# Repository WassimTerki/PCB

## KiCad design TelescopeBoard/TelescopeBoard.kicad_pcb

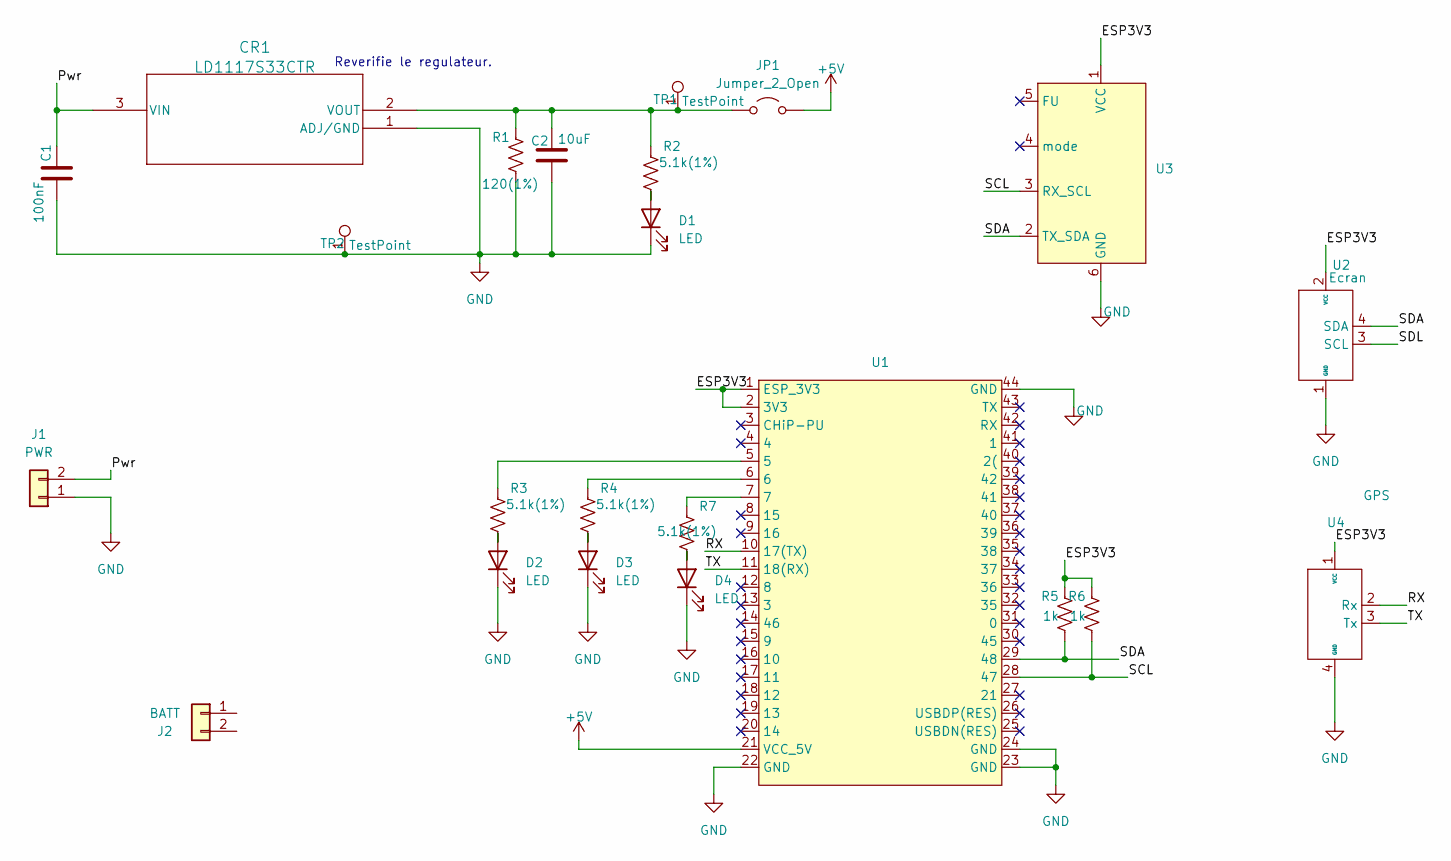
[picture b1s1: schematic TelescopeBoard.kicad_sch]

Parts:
C1: 100nF; C_0805_2012Metric_Pad1.18x1.45mm_HandSolder
C2: 10uF; C_0805_2012Metric_Pad1.18x1.45mm_HandSolder
CR1: LD1117S33CTR; careguleiciouuuuuuuuu
D1, D2, D3, D4: LED; LED_LTST-C_LTO
J1: PWR; PinHeader_1x02_P2.54mm_Vertical
J2: BATT; conn2
JP1: Jumper_2_Open; PinHeader_1x02_P2.54mm_Vertical
R1: 120(1%); R_0805_2012Metric
R2, R3, R4, R7: 5.1k(1%); R_0805_2012Metric
R5, R6: 1k; R_0805_2012Metric
TP1, TP2: TestPoint; PinHeader_1x01_P2.54mm_Vertical
U1: MY SHIT
U2: Ecran; PinHeader_1x04_P2.54mm_Vertical
U3: PinHeader_1x06_P2.54mm_Vertical
U4: GPS; PinHeader_1x04_P2.54mm_Vertical

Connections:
+5V: JP1.2 (B), U1.21 (VCC_5V)
/ESP3V3: R5.2, R6.2, U1.1 (ESP_3V3), U1.2 (3V3), U2.2 (VCC), U3.1 (VCC), U4.1 (VCC)
/Pwr: C1.1, CR1.3 (VIN), J1.2
/RX: U1.10 (17(TX)), U4.2 (Rx)
/SCL: R6.1, U1.28 (47), U3.3 (RX_SCL)
/SDA: R5.1, U1.29 (48), U2.4 (SDA), U3.2 (TX_SDA)
/SDL: U2.3 (SCL)
/TX: U1.11 (18(RX)), U4.3 (Tx)
GND: C1.2, C2.2, CR1.1 (ADJ/GND), D1.1 (K), D2.1 (K), D3.1 (K), D4.1 (K), J1.1, R1.1, TP2.1, U1.22 (GND), U1.23 (GND), U1.24 (GND), U1.44 (GND), U2.1 (GND), U3.6 (GND), U4.4 (GND)
unnamed: C2.1, CR1.2 (VOUT), JP1.1 (A), R1.2, R2.2, TP1.1
unnamed: D1.2 (A), R2.1
unnamed: D2.2 (A), R3.1
unnamed: D3.2 (A), R4.1
unnamed: D4.2 (A), R7.1
unnamed: R3.2, U1.5
unnamed: R4.2, U1.6
unnamed: R7.2, U1.7

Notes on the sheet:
Reverifie le regulateur.

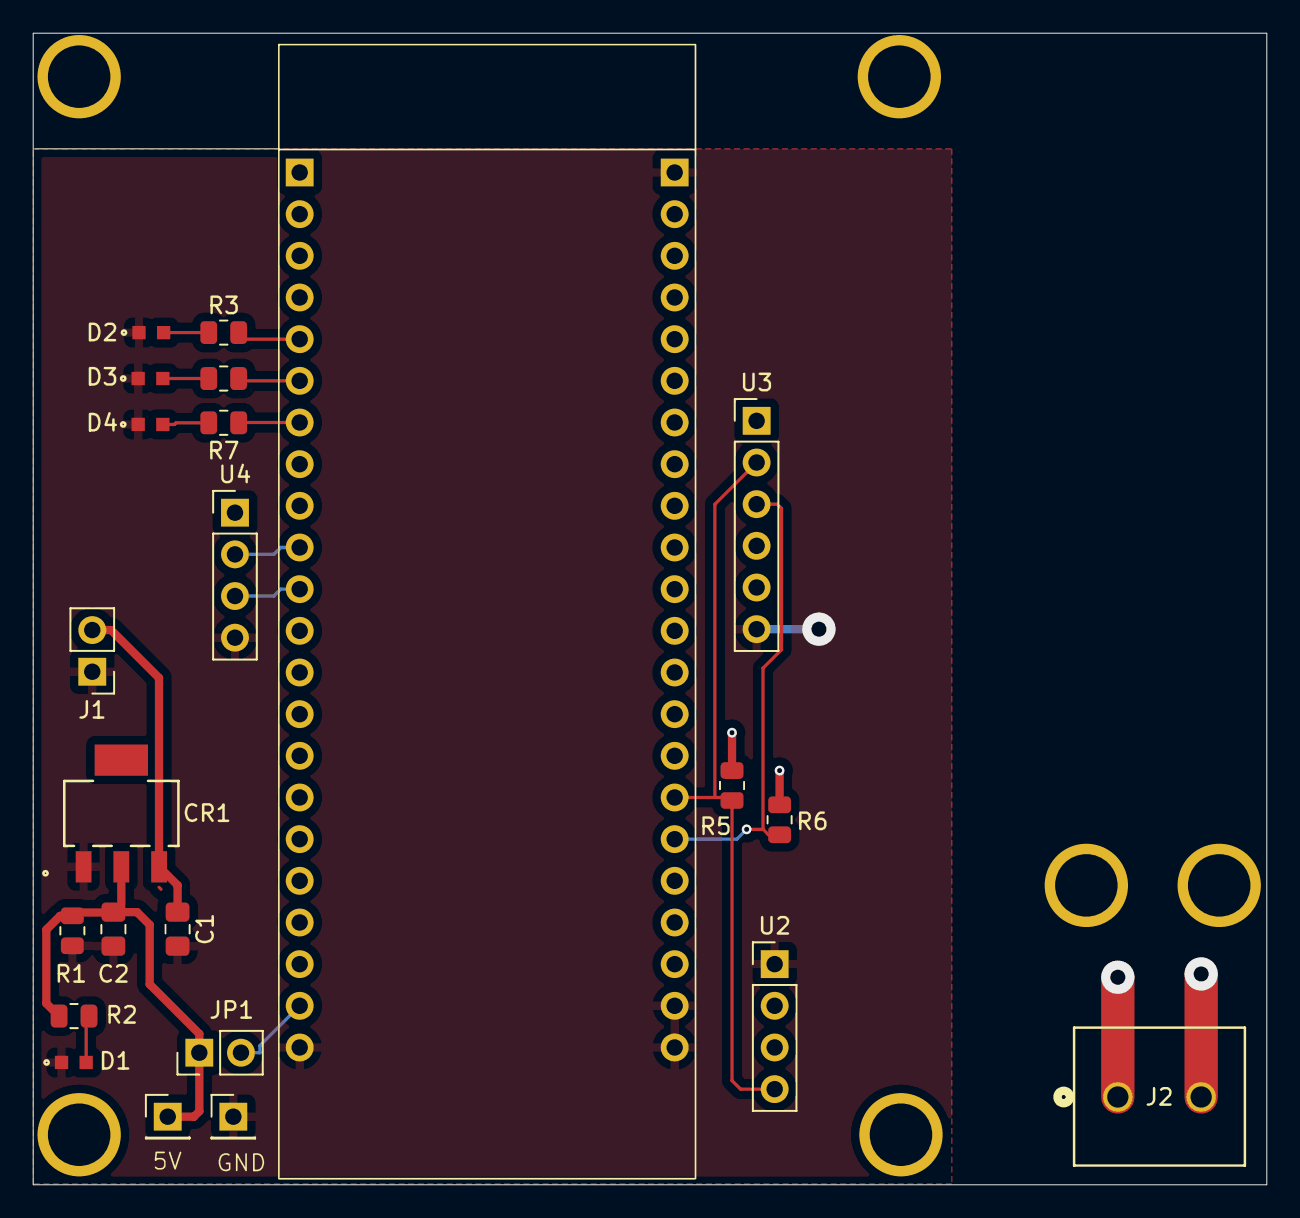
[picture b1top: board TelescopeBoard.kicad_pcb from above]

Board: 2 copper layers, 75.2 x 70.2 mm, 23 parts (0 on the bottom side), 16 nets.

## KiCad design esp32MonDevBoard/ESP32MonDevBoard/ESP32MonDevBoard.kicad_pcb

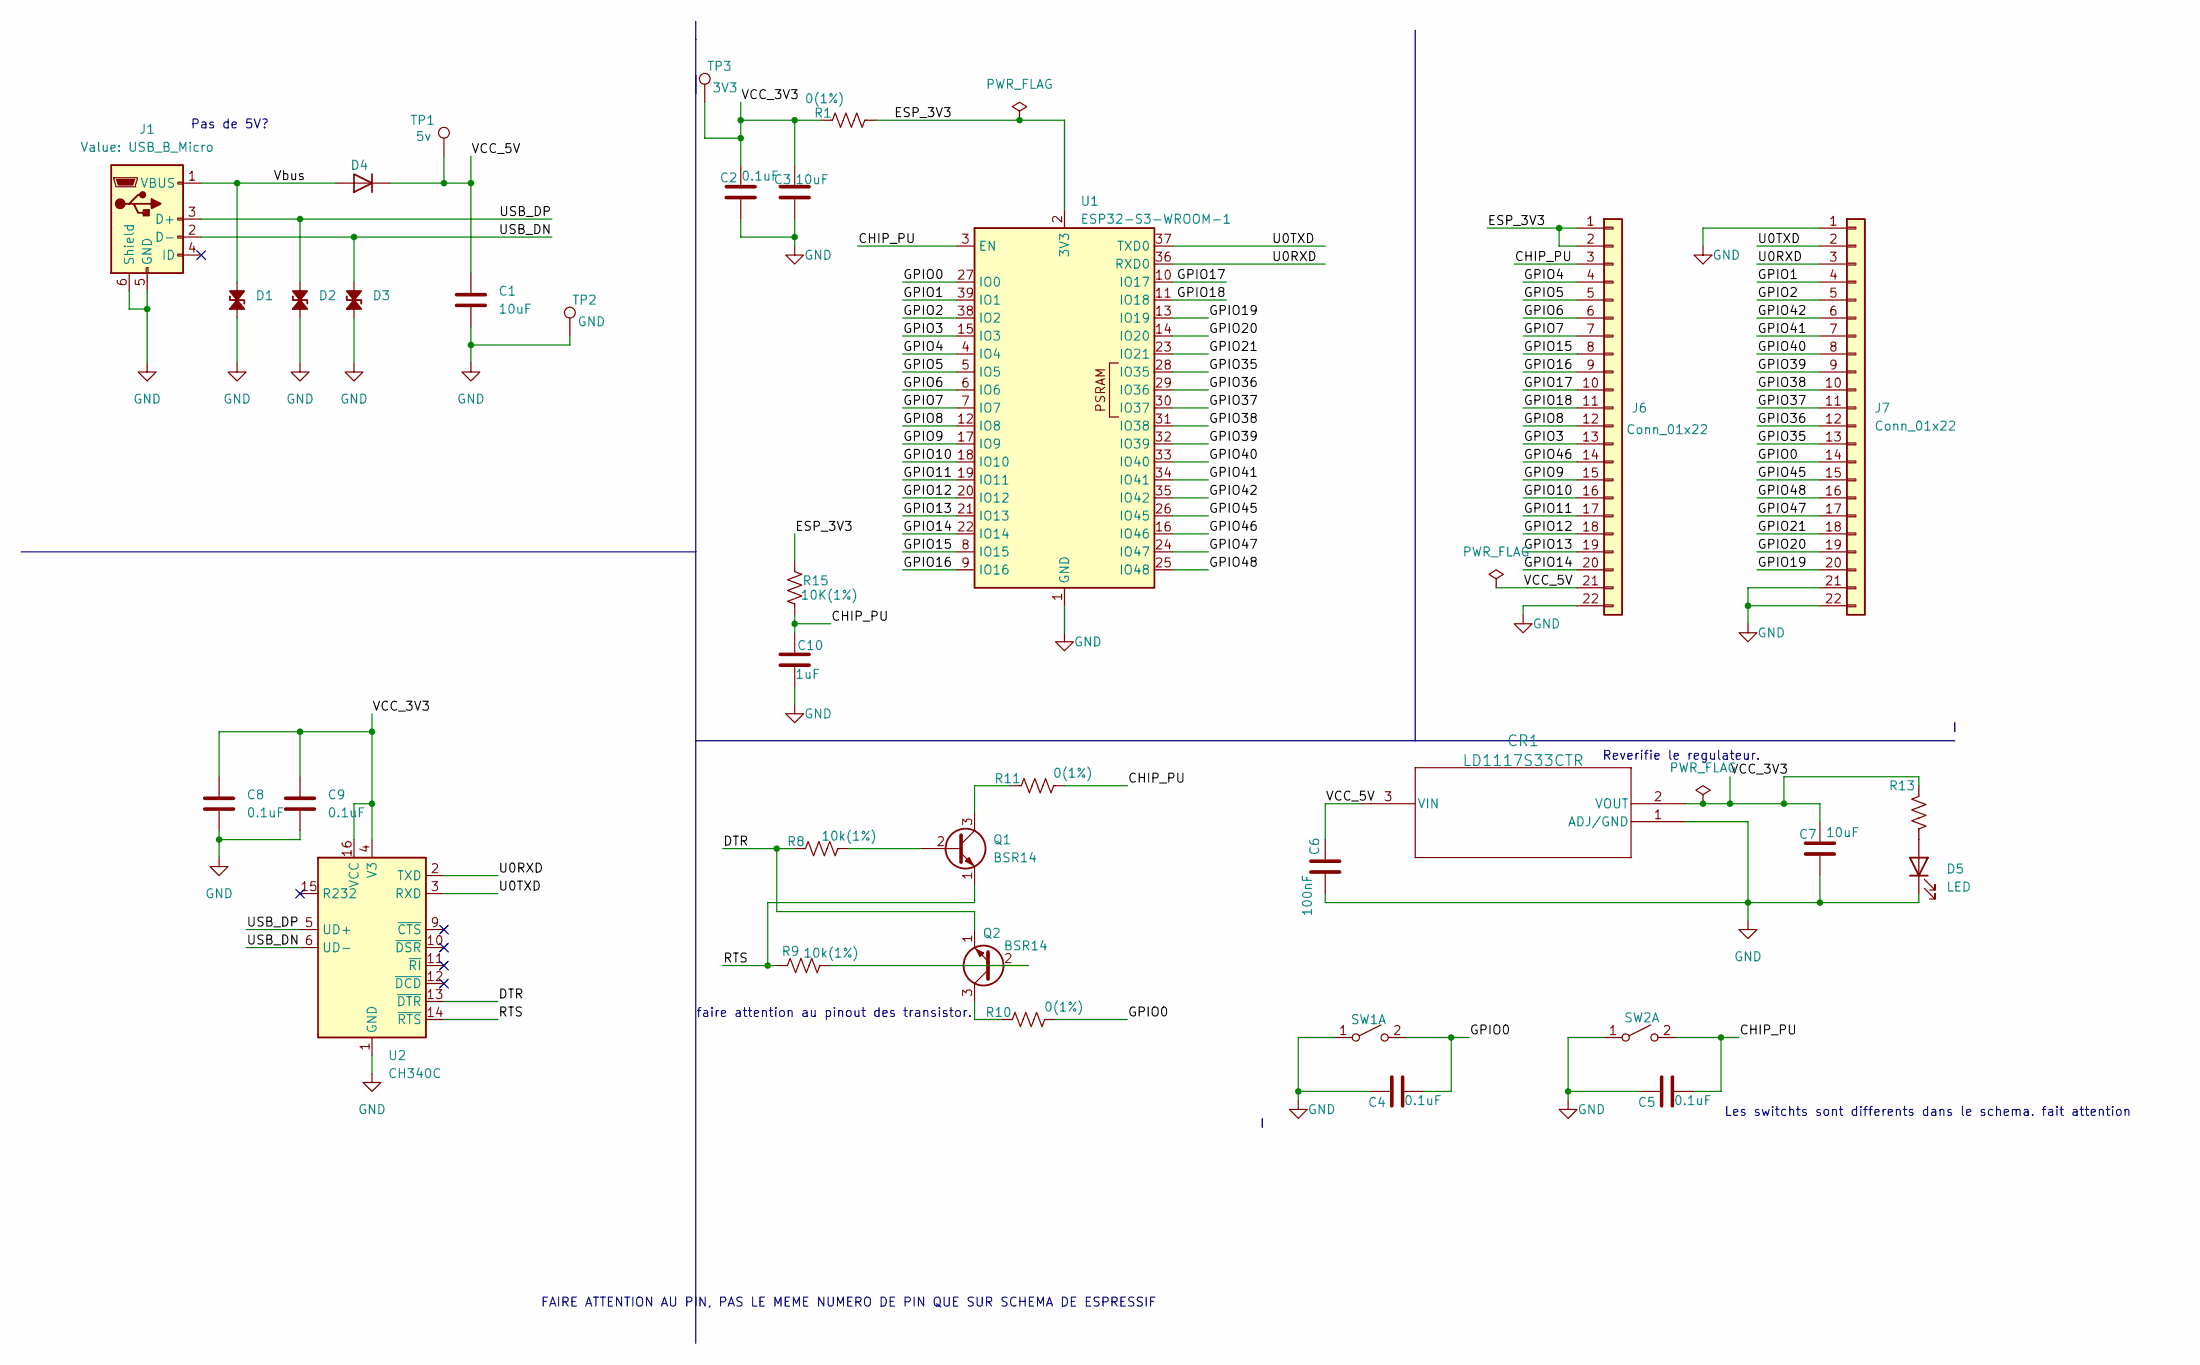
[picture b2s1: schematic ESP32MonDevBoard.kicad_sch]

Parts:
C1, C3, C7: 10uF; C_0805_2012Metric_Pad1.18x1.45mm_HandSolder
C2, C4, C5, C8, C9: 0.1uF; C_0805_2012Metric_Pad1.18x1.45mm_HandSolder
C6: 100nF; C_0805_2012Metric_Pad1.18x1.45mm_HandSolder
C10: 1uF; C_0805_2012Metric_Pad1.18x1.45mm_HandSolder
CR1: LD1117S33CTR; careguleiciouuuuuuuuu
D1, D2, D3: DODEBIZ
D4: dode
D5: LED; LED_LTST-C_LTO
J1: USB_B_Micro; CONN_10118192-0002LF_AMP
J6, J7: Conn_01x22; PinHeader_1x22_P2.54mm_Vertical
Q1, Q2: BSR14; transistor
R1, R10, R11: 0(1%); R_0805_2012Metric
R8, R9: 10k(1%); R_0805_2012Metric
R13: R_0805_2012Metric
R15: 10K(1%); R_0805_2012Metric
SW1, SW2: rien a signaler
TP1: 5v; PinHeader_1x01_P2.54mm_Vertical
TP2: GND; PinHeader_1x01_P2.54mm_Vertical
TP3: 3V3; PinHeader_1x01_P2.54mm_Vertical
U1: ESP32-S3-WROOM-1
U2: CH340C; SOIC-16_3.9x9.9mm_P1.27mm

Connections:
/CHIP_PU: C5.2, C10.1, J6.3, R11.2, R15.2, SW2.2 (B), U1.3 (EN)
/DTR: Q2.1 (E), R8.1, U2.13 (~DTR)
/ESP_3V3: J6.1, J6.2, R1.2, R15.1, U1.2 (3V3)
/GPIO0: C4.2, J7.14, R10.2, SW1.2 (B), U1.27 (IO0)
/GPIO1: J7.4, U1.39 (IO1)
/GPIO2: J7.5, U1.38 (IO2)
/GPIO3: J6.13, U1.15 (IO3)
/GPIO4: J6.4, U1.4 (IO4)
/GPIO5: J6.5, U1.5 (IO5)
/GPIO6: J6.6, U1.6 (IO6)
/GPIO7: J6.7, U1.7 (IO7)
/GPIO8: J6.12, U1.12 (IO8)
/GPIO9: J6.15, U1.17 (IO9)
/GPIO10: J6.16, U1.18 (IO10)
/GPIO11: J6.17, U1.19 (IO11)
/GPIO12: J6.18, U1.20 (IO12)
/GPIO13: J6.19, U1.21 (IO13)
/GPIO14: J6.20, U1.22 (IO14)
/GPIO15: J6.8, U1.8 (IO15)
/GPIO16: J6.9, U1.9 (IO16)
/GPIO17: J6.10, U1.10 (IO17)
/GPIO18: J6.11, U1.11 (IO18)
/GPIO19: J7.20, U1.13 (IO19)
/GPIO20: J7.19, U1.14 (IO20)
/GPIO21: J7.18, U1.23 (IO21)
/GPIO35: J7.13, U1.28 (IO35)
/GPIO36: J7.12, U1.29 (IO36)
/GPIO37: J7.11, U1.30 (IO37)
/GPIO38: J7.10, U1.31 (IO38)
/GPIO39: J7.9, U1.32 (IO39)
/GPIO40: J7.8, U1.33 (IO40)
/GPIO41: J7.7, U1.34 (IO41)
/GPIO42: J7.6, U1.35 (IO42)
/GPIO45: J7.15, U1.26 (IO45)
/GPIO46: J6.14, U1.16 (IO46)
/GPIO47: J7.17, U1.24 (IO47)
/GPIO48: J7.16, U1.25 (IO48)
/RTS: Q1.1 (E), R9.1, U2.14 (~RTS)
/U0RXD: J7.3, U1.36 (RXD0), U2.2 (TXD)
/U0TXD: J7.2, U1.37 (TXD0), U2.3 (RXD)
/USB_DN: D3.2 (A2), J1.2 (D-), U2.6 (UD-)
/USB_DP: D2.2 (A2), J1.3 (D+), U2.5 (UD+)
/VCC_3V3: C2.1, C3.1, C7.1, C8.1, C9.1, CR1.2 (VOUT), R1.1, R13.2, TP3.1, U2.4 (V3), U2.16 (VCC)
/VCC_5V: C1.1, C6.1, CR1.3 (VIN), D4.1 (K), J6.21, TP1.1
/Vbus: D1.2 (A2), D4.2 (A), J1.1 (VBUS)
GND: C1.2, C2.2, C3.2, C4.1, C5.1, C6.2, C7.2, C8.2, C9.2, C10.2, CR1.1 (ADJ/GND), D1.1 (A1), D2.1 (A1), D3.1 (A1), D5.1 (K), J1.5 (GND), J1.6 (Shield), J6.22, J7.1, J7.21, J7.22, SW1.1 (A), SW2.1 (A), TP2.1, U1.1 (GND), U1.40 (GND), U1.41 (GND), U2.1 (GND)
unnamed: D5.2 (A), R13.1
unnamed: Q1.2 (B), R8.2
unnamed: Q1.3 (C), R11.1
unnamed: Q2.2 (B), R9.2
unnamed: Q2.3 (C), R10.1

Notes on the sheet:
Pas de 5V?
Reverifie le regulateur.
FAIRE ATTENTION AU PIN, PAS LE MEME NUMERO DE PIN QUE SUR SCHEMA DE ESPRESSIF
faire attention au pinout des transistor.
Les switchts sont differents dans le schema. fait attention

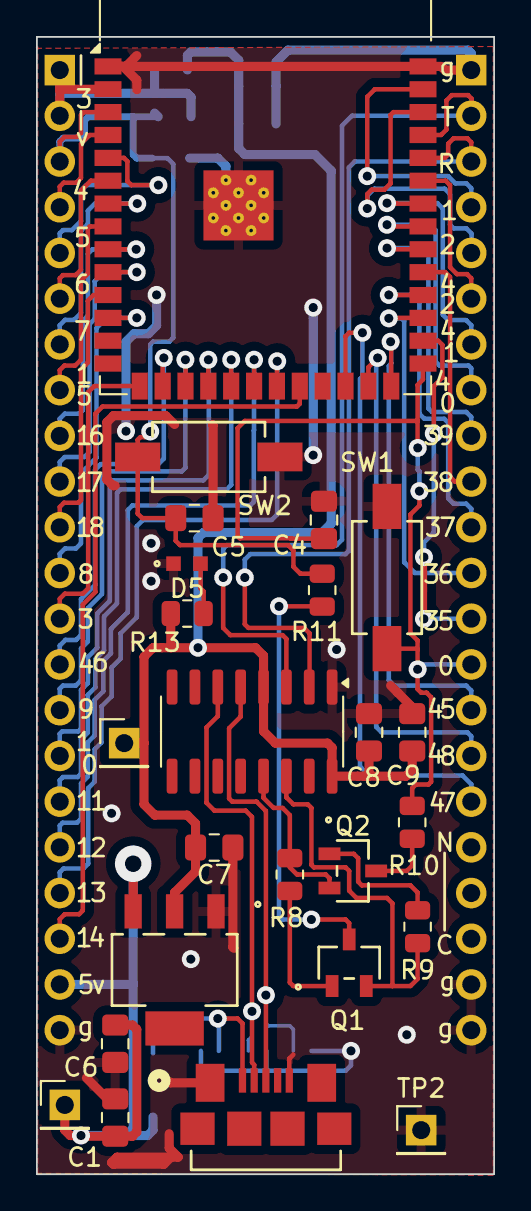
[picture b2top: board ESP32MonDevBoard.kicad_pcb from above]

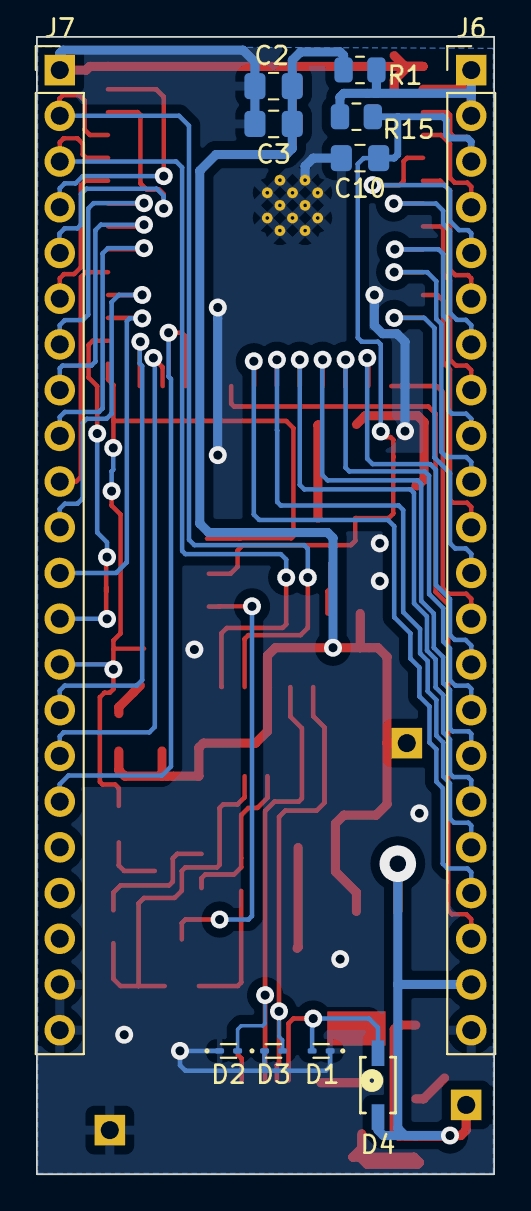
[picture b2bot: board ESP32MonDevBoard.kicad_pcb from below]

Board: 2 copper layers, 25.4 x 63.2 mm, 35 parts (11 on the bottom side), 51 nets.

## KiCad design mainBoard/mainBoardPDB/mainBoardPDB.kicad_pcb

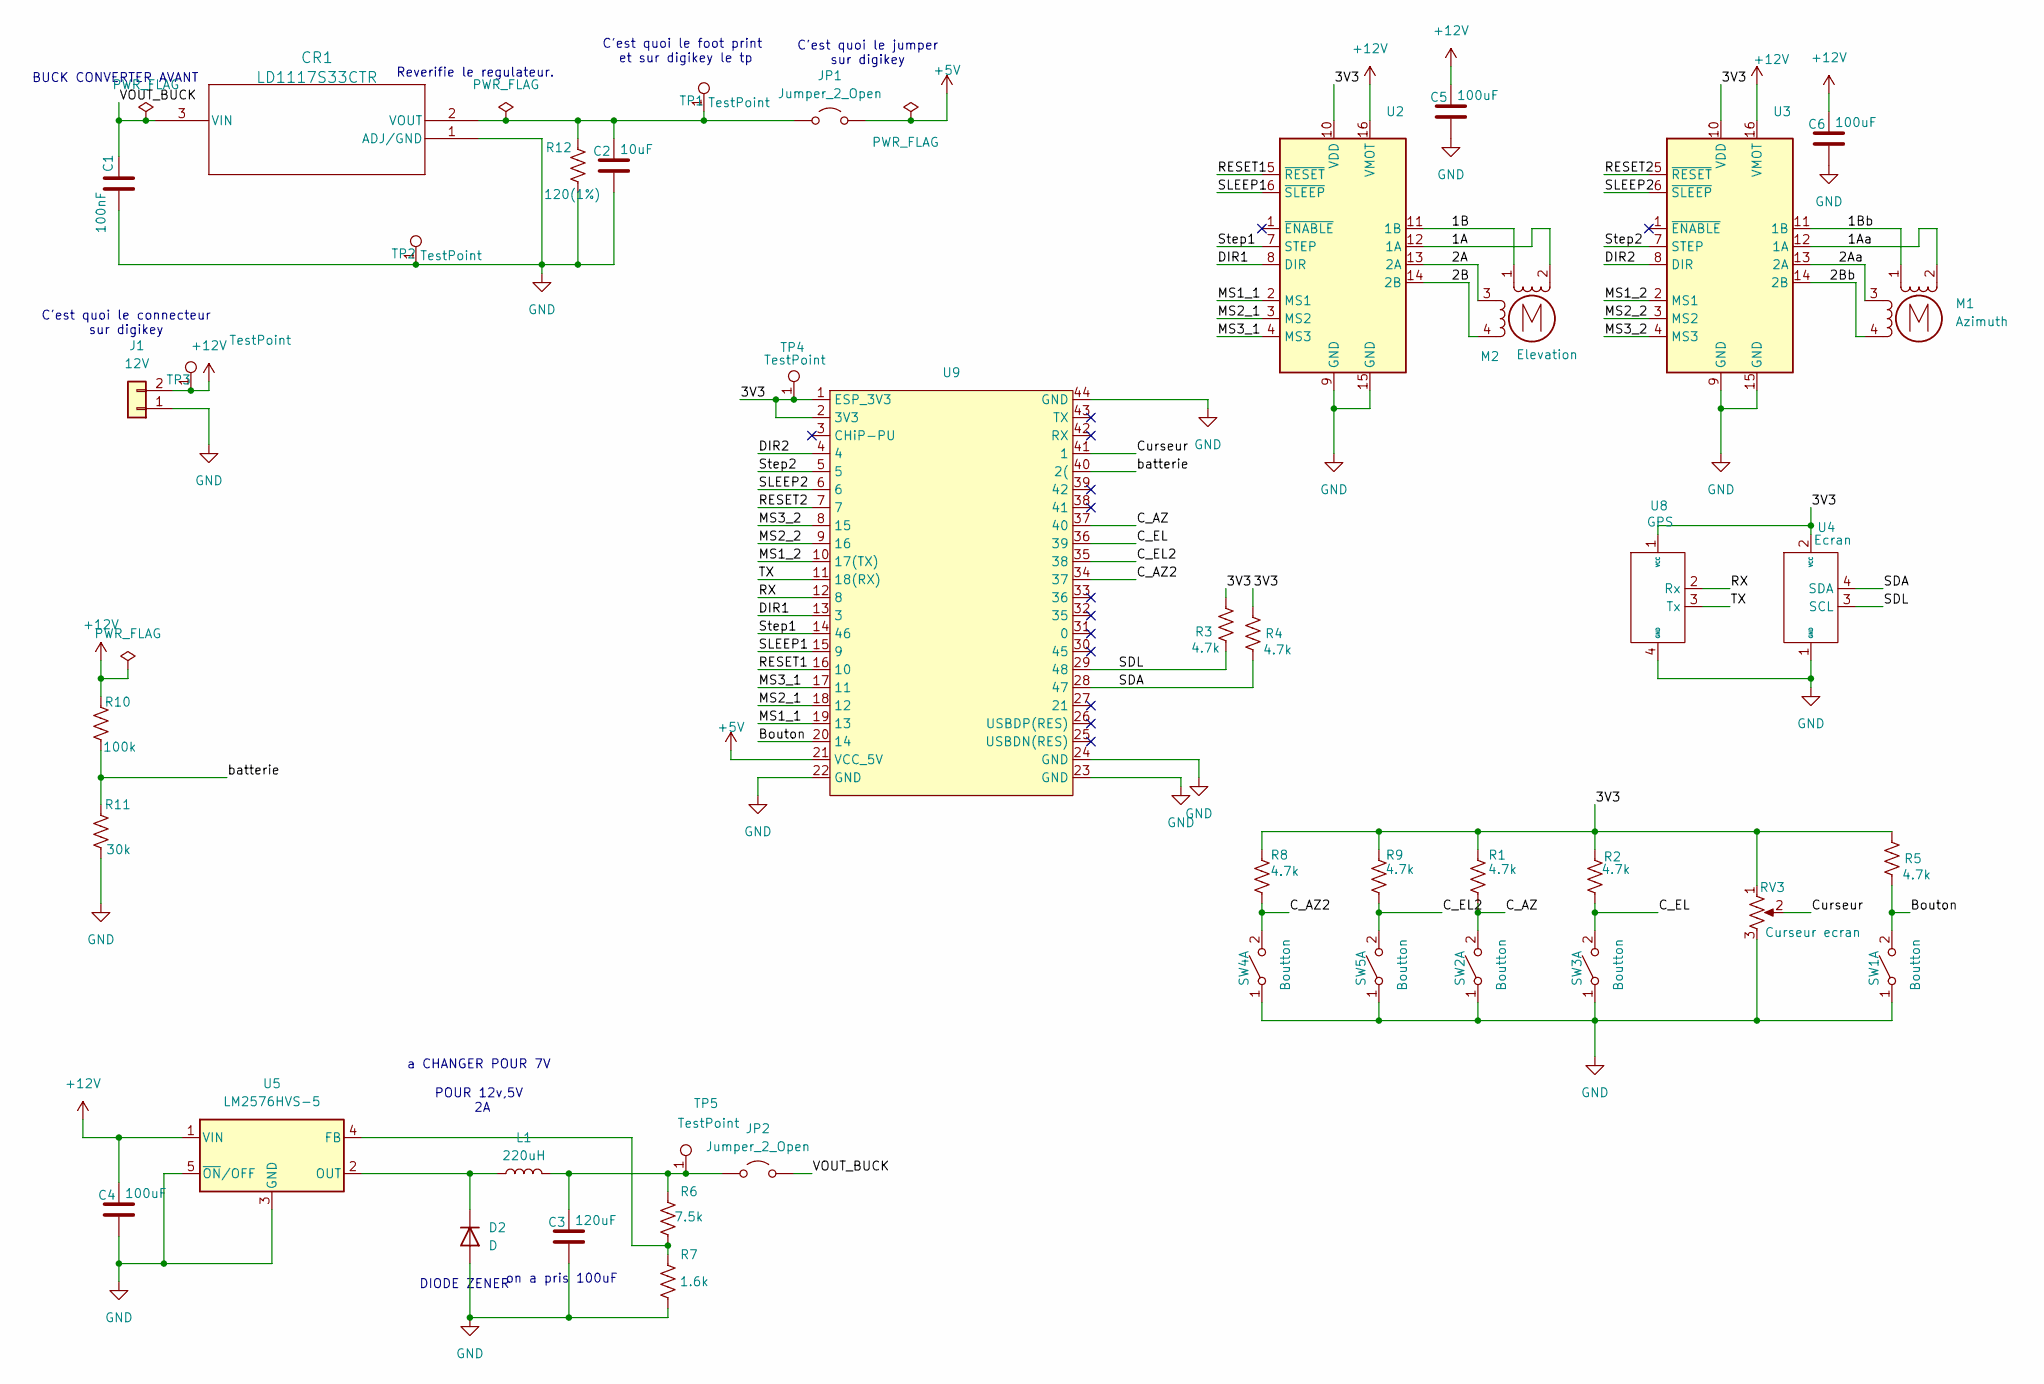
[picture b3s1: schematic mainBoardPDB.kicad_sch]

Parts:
C1: 100nF; C_0805_2012Metric
C2: 10uF; C_0805_2012Metric
C3: 120uF; C_1210_3225Metric_Pad1.33x2.70mm_HandSolder
C4, C5, C6: 100uF; C_1210_3225Metric_Pad1.33x2.70mm_HandSolder
CR1: LD1117S33CTR; SOT-223-5
D2: D; DIODE
J1: 12V; PinHeader_1x02_P2.54mm_Vertical
JP1, JP2: Jumper_2_Open; PinHeader_1x02_P2.54mm_Vertical
L1: 220uH; Bobine
M1: Azimuth; PinHeader_1x04_P2.54mm_Vertical
M2: Elevation; PinHeader_1x04_P2.54mm_Vertical
R1, R2, R3, R4, R5, R8, R9: 4.7k; R_0805_2012Metric
R6: 7.5k; R_0805_2012Metric
R7: 1.6k; R_0805_2012Metric
R10: 100k; R_0805_2012Metric
R11: 30k; R_0805_2012Metric
R12: 120(1%); R_0805_2012Metric
RV3: Curseur ecran; Potentiometer_Alps_RK09K_Single_Vertical
SW1, SW2, SW3, SW4, SW5: Boutton; 3pointswichpdv
TP1, TP2, TP3, TP4, TP5: TestPoint; PinHeader_1x01_P2.54mm_Vertical
U2, U3: VROOMVROOM
U4: Ecran; PinHeader_1x04_P2.00mm_Vertical
U5: LM2576HVS-5; TO-263-5_TabPin3
U8: GPS; PinHeader_1x04_P2.00mm_Vertical
U9: MY SHIT

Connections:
+5V: JP1.2 (B), U9.21 (VCC_5V)
+12V: C4.1, C5.1, C6.1, J1.2, R10.2, TP3.1, U2.16 (VMOT), U3.16 (VMOT), U5.1 (VIN)
/1A: M2.2 (-), U2.12 (1A)
/1Aa: M1.2 (-), U3.12 (1A)
/1B: M2.1, U2.11 (1B)
/1Bb: M1.1, U3.11 (1B)
/2A: M2.3, U2.13 (2A)
/2Aa: M1.3, U3.13 (2A)
/2B: M2.4, U2.14 (2B)
/2Bb: M1.4, U3.14 (2B)
/3V3: R1.2, R2.2, R3.2, R4.2, R5.2, R8.2, R9.2, RV3.1, TP4.1, U2.10 (VDD), U3.10 (VDD), U4.2 (VCC), U8.1 (VCC), U9.1 (ESP_3V3), U9.2 (3V3)
/Bouton: R5.1, SW1.2 (B), U9.20 (14)
/C_AZ: R1.1, SW2.2 (B), U9.37 (40)
/C_AZ2: R8.1, SW4.2 (B), U9.34 (37)
/C_EL: R2.1, SW3.2 (B), U9.36 (39)
/C_EL2: R9.1, SW5.2 (B), U9.35 (38)
/Curseur: RV3.2, U9.41 (1)
/DIR1: U2.8 (DIR), U9.13 (3)
/DIR2: U3.8 (DIR), U9.4
/MS1_1: U2.2 (MS1), U9.19 (13)
/MS1_2: U3.2 (MS1), U9.10 (17(TX))
/MS2_1: U2.3 (MS2), U9.18 (12)
/MS2_2: U3.3 (MS2), U9.9 (16)
/MS3_1: U2.4 (MS3), U9.17 (11)
/MS3_2: U3.4 (MS3), U9.8 (15)
/RESET1: U2.5 (~RESET), U9.16 (10)
/RESET2: U3.5 (~RESET), U9.7
/RX: U8.2 (Rx), U9.12 (8)
/SDA: R4.1, U4.4 (SDA), U9.28 (47)
/SDL: R3.1, U4.3 (SCL), U9.29 (48)
/SLEEP1: U2.6 (~SLEEP), U9.15 (9)
/SLEEP2: U3.6 (~SLEEP), U9.6
/Step1: U2.7 (STEP), U9.14 (46)
/Step2: U3.7 (STEP), U9.5
/TX: U8.3 (Tx), U9.11 (18(RX))
/VOUT_BUCK: C1.1, CR1.3 (VIN), JP2.2 (B)
/batterie: R10.1, R11.2, U9.40 (2()
GND: C1.2, C2.2, C3.2, C4.2, C5.2, C6.2, CR1.1 (ADJ/GND), D2.2 (A), J1.1, R7.1, R11.1, R12.1, RV3.3, SW1.1 (A), SW2.1 (A), SW3.1 (A), SW4.1 (A), SW5.1 (A), TP2.1, U2.9 (GND), U2.15 (GND), U3.9 (GND), U3.15 (GND), U4.1 (GND), U5.3 (GND), U5.5 (~ON/OFF), U8.4 (GND), U9.22 (GND), U9.23 (GND), U9.24 (GND), U9.44 (GND)
unnamed: C2.1, CR1.2 (VOUT), JP1.1 (A), R12.2, TP1.1
unnamed: D2.1 (K), L1.1, U5.2 (OUT)
unnamed: C3.1, JP2.1 (A), L1.2, R6.2, TP5.1
unnamed: R6.1, R7.2, U5.4 (FB)

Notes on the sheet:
C'est quoi le jumper sur digikey
on a pris 100uF
a CHANGER POUR 7V POUR 12v,5V 2A
C'est quoi le connecteur sur digikey
BUCK CONVERTER AVANT
DIODE ZENER
Reverifie le regulateur.
C'est quoi le foot print et sur digikey le tp

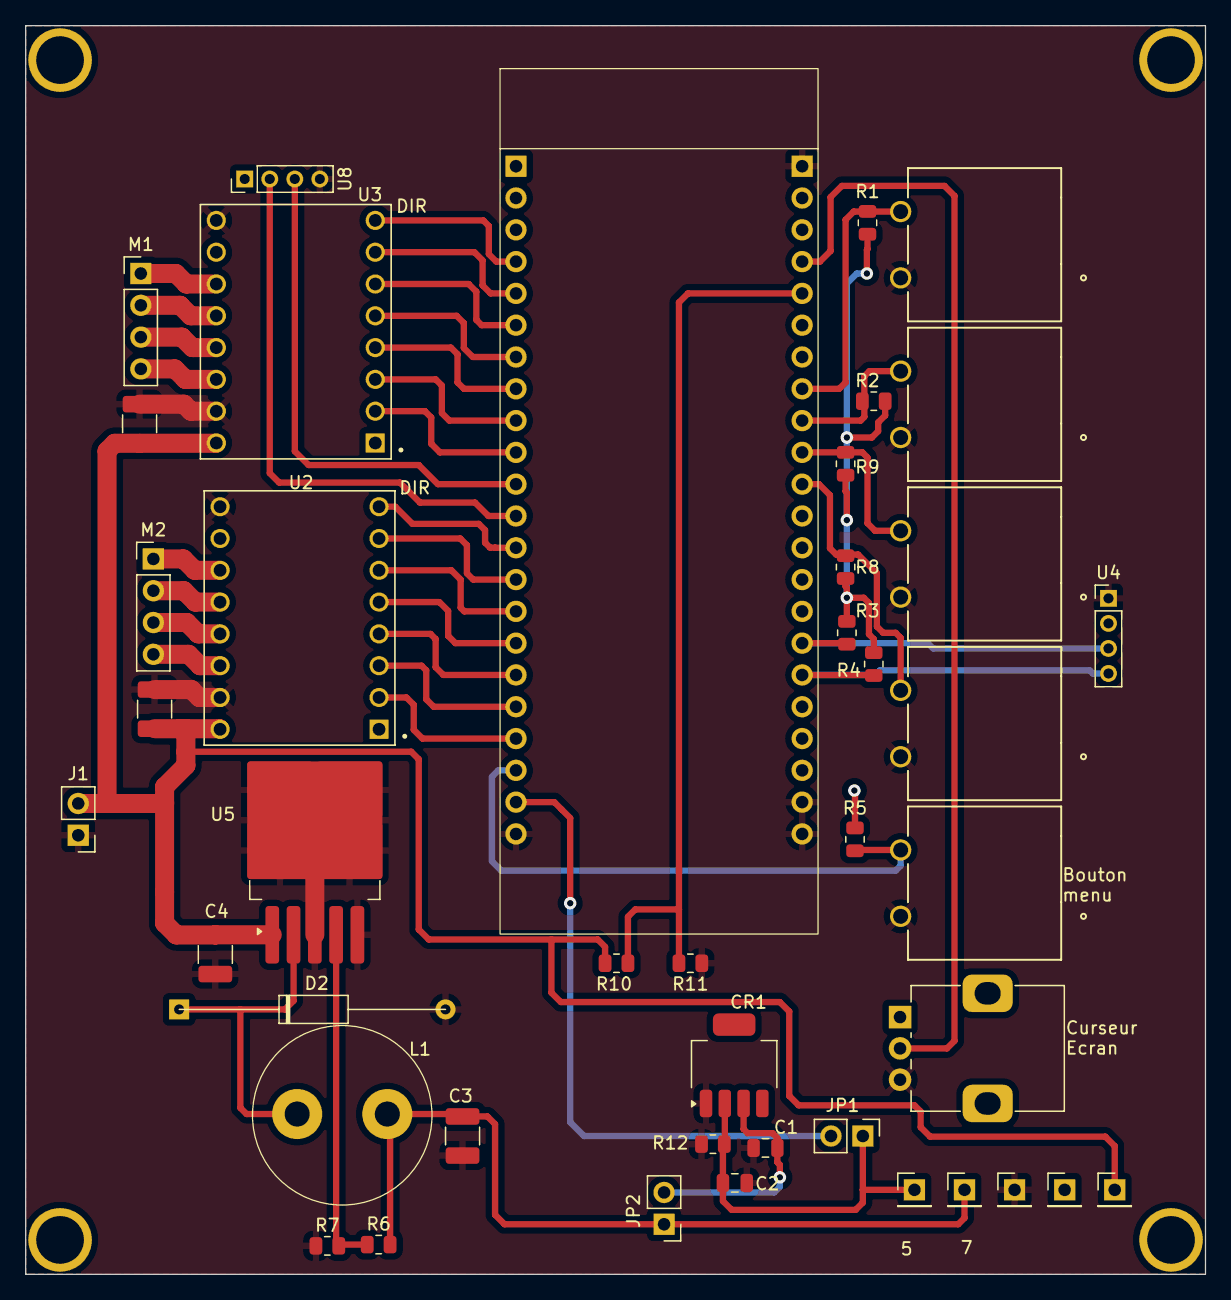
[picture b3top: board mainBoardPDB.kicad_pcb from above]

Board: 2 copper layers, 94.2 x 99.8 mm, 43 parts (0 on the bottom side), 42 nets.
